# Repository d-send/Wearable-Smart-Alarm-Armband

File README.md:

# Wearable Smart Alarm Armband (Work in progress)

An Armband designed primaraly for force waking up in the morning using vibration and Electrical stimulation.Uses an android app to communicate via BLE for scheuling and monitering status such as battery capacity.Integrated IMU is used to detect weather the user is awake or sleeping.

## Features
* Wakeup sheduling capability through an android app via BLE
* reminders through vibrations
* two hardware buttons for additional functionalities
* extremely low power consumption
* detachable battery
* tightness adjestable strip (around arm)  

## PCB

## Finished Armband

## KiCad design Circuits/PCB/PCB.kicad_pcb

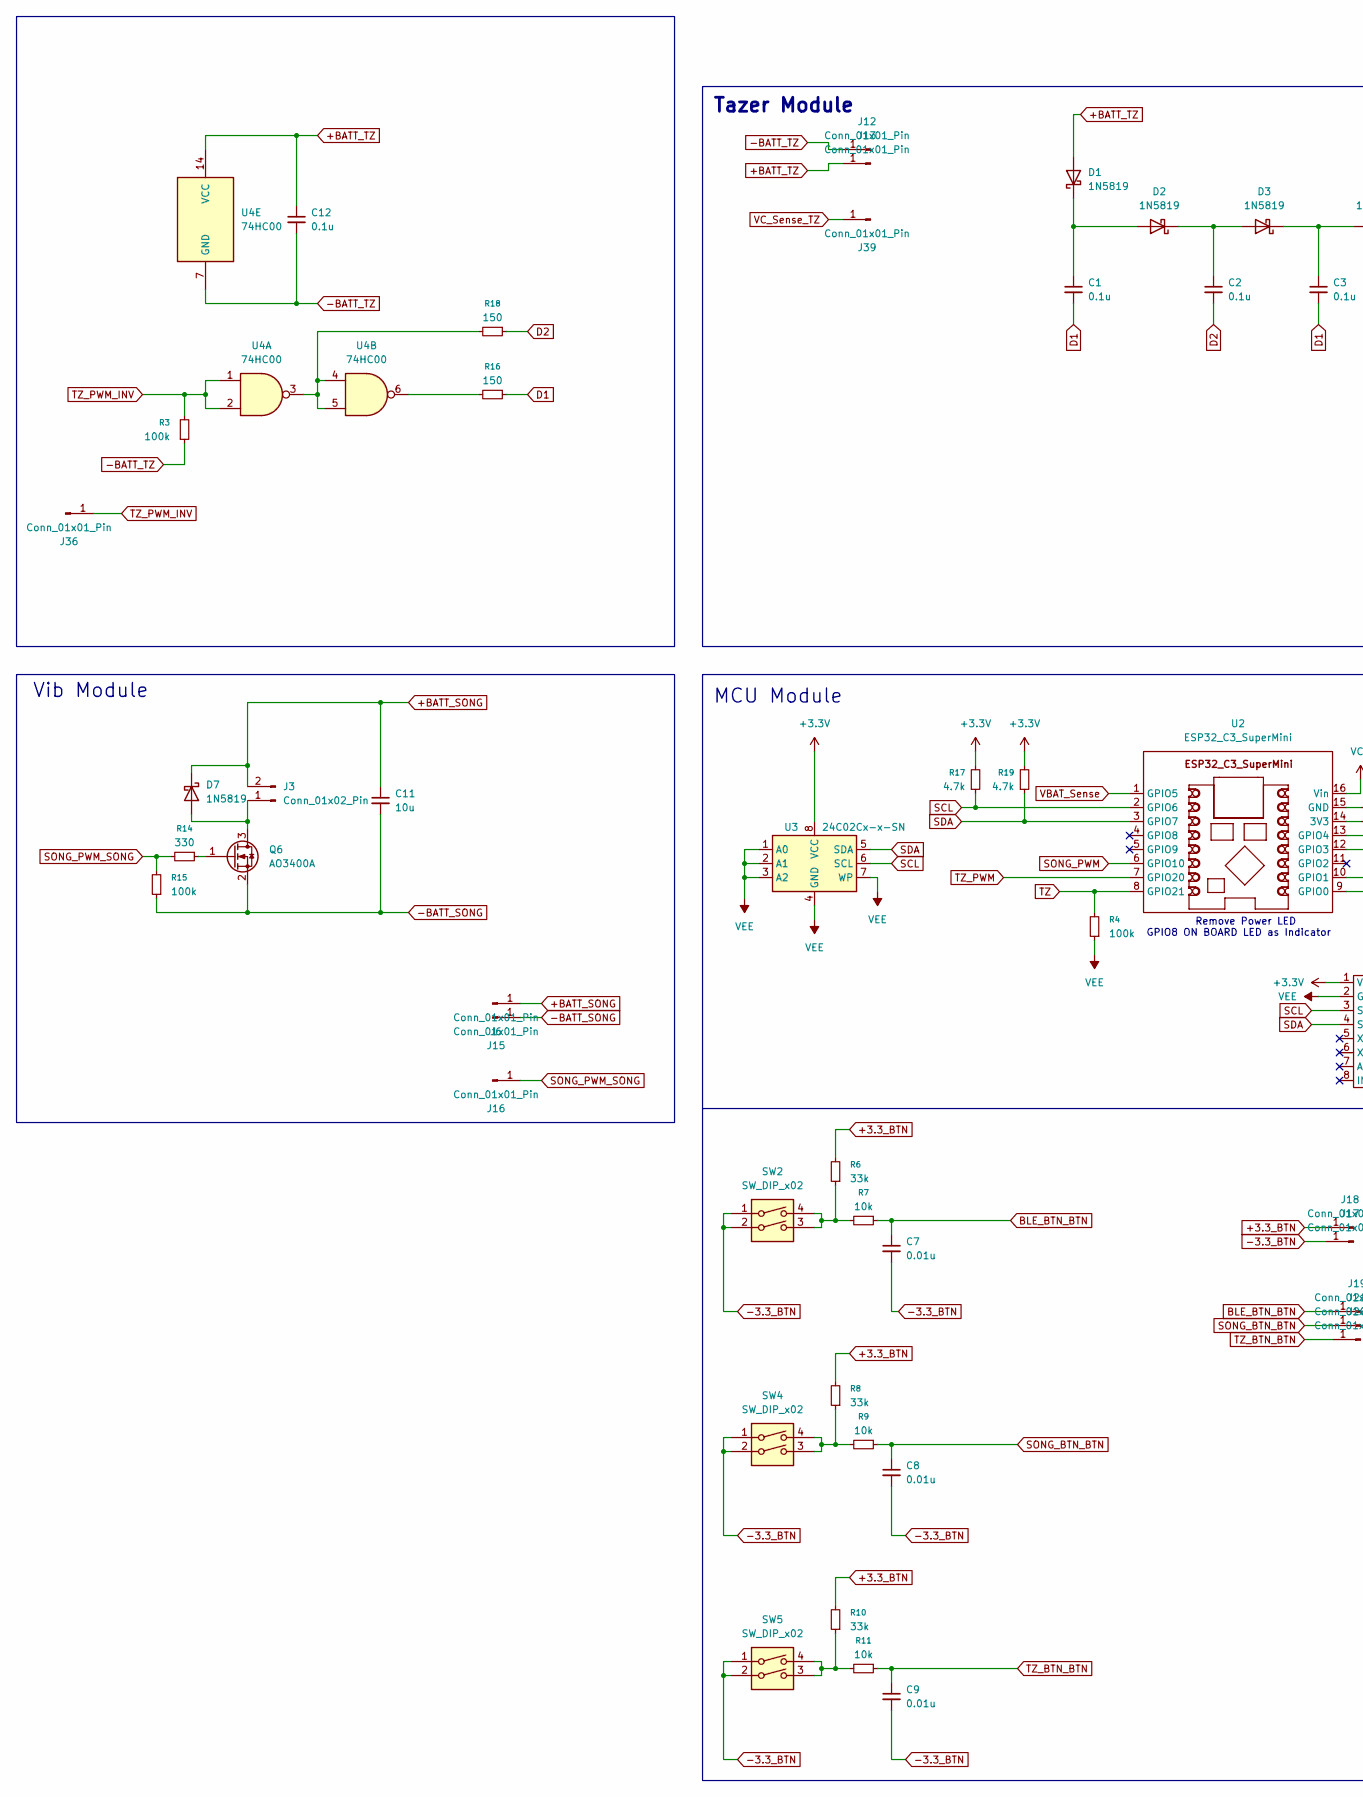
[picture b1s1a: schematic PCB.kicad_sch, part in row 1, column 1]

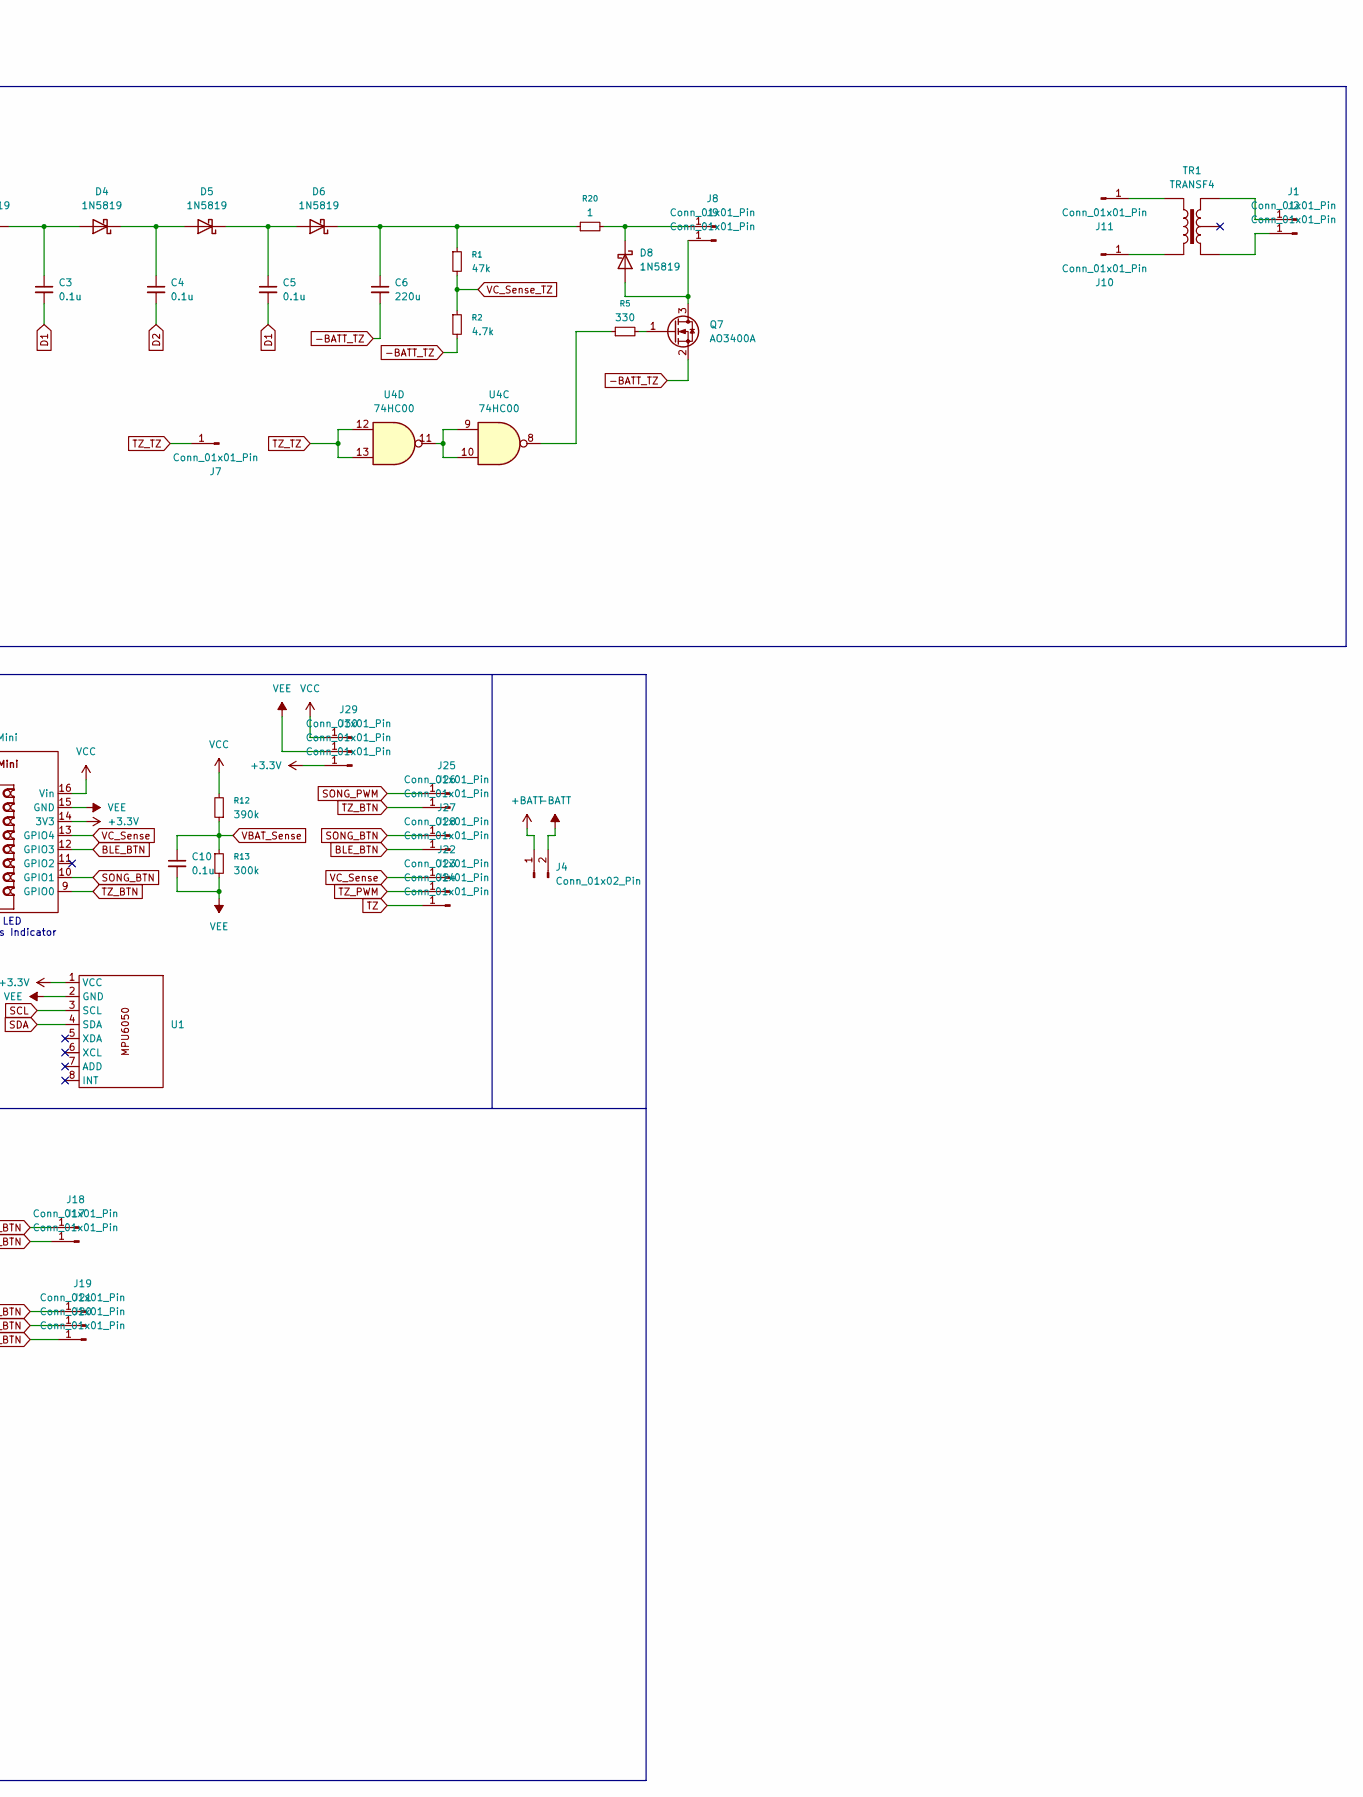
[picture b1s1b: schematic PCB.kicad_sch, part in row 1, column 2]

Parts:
C1, C2, C3, C4, C5, C10, C12: 0.1u; C_Disc_D5.0mm_W2.5mm_P2.50mm
C6: 220u; CP_Radial_D8.0mm_P3.80mm
C7, C8, C9: 0.01u; C_Disc_D5.0mm_W2.5mm_P2.50mm
C11: 10u; CP_Radial_D5.0mm_P2.50mm
D1, D2, D3, D4, D5, D6, D7, D8: 1N5819; D_DO-41_SOD81_P7.62mm_Horizontal
J1, J2: Conn_01x01_Pin; TestPoint_THTPad_2.0x2.0mm_Drill1.0mm
J3: Conn_01x02_Pin; TestPoint_2Pads_Pitch2.54mm_Drill0.8mm
J4: Conn_01x02_Pin; JST_XH_B2B-XH-A_1x02_P2.50mm_Vertical
J6, J7, J8, J9, J10, J11, J12, J13, J15, J16, J17, J18, J19, J20, J21, J22, J23, J24, J25, J26, J27, J28, J29, J30, J33, J36, J39: Conn_01x01_Pin; TestPoint_THTPad_D1.5mm_Drill0.7mm
Q6, Q7: AO3400A; SOT-23
R1: 47k; R_0603_1608Metric
R2, R17, R19: 4.7k; R_0603_1608Metric
R3, R15: 100k; R_Axial_DIN0207_L6.3mm_D2.5mm_P7.62mm_Horizontal
R4: 100k; R_Axial_DIN0207_L6.3mm_D2.5mm_P10.16mm_Horizontal
R5, R14: 330; R_Axial_DIN0207_L6.3mm_D2.5mm_P7.62mm_Horizontal
R6, R8, R10: 33k; R_0603_1608Metric
R7, R9, R11: 10k; R_0603_1608Metric
R12: 390k; R_1206_3216Metric
R13: 300k; R_1206_3216Metric
R16, R18: 150; R_1206_3216Metric
R20: 1; R_1206_3216Metric
SW2, SW4, SW5: SW_DIP_x02; DPDT_Switch
TR1: TRANSF4; 5pin Flyback Transformer
U1: MPU6050_Module
U2: ESP32_C3_SuperMini
U3: 24C02Cx-x-SN; DIP-8_W7.62mm
U4: 74HC00; DIP-14_W7.62mm

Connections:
+3.3V: J33.1, R17.2, R19.2, U1.1 (VCC), U2.14 (3V3), U3.8 (VCC)
+3.3_BTN: J18.1, R6.2, R8.2, R10.2
+BATT: J4.1
+BATT_SONG: C11.1, D7.1 (K), J3.2, J6.1
+BATT_TZ: C12.1, D1.2 (A), J13.1, U4.14 (VCC)
-3.3_BTN: C7.2, C8.2, C9.2, J17.1, SW2.1, SW2.2, SW4.1, SW4.2, SW5.1, SW5.2
-BATT: J4.2
-BATT_SONG: C11.2, J15.1, Q6.2 (S), R15.1
-BATT_TZ: C6.2, C12.2, J12.1, Q7.2 (S), R2.2, R3.1, U4.7 (GND)
BLE_BTN: J28.1, U2.12 (GPIO3)
BLE_BTN_BTN: C7.1, J19.1, R7.1
D1: C1.2, C3.2, C5.2, R16.1; also elsewhere on the board
D2: C2.2, C4.2, R18.1; also elsewhere on the board
unnamed: C1.1, D1.1 (K), D2.2 (A)
unnamed: C2.1, D2.1 (K), D3.2 (A)
unnamed: C3.1, D3.1 (K), D4.2 (A)
unnamed: C4.1, D4.1 (K), D5.2 (A)
unnamed: C5.1, D5.1 (K), D6.2 (A)
unnamed: C6.1, D6.1 (K), R1.1, R20.1
unnamed: D7.2 (A), J3.1, Q6.3 (D)
unnamed: D8.2 (A), J9.1, Q7.3 (D)
unnamed: D8.1 (K), J8.1, R20.2
unnamed: J1.1, TR1.3
unnamed: J2.1, TR1.1
unnamed: J10.1, TR1.5
unnamed: J11.1, TR1.4
unnamed: Q6.1 (G), R14.1
unnamed: Q7.1 (G), R5.2
unnamed: R5.1, U4.8
unnamed: R6.1, R7.2, SW2.3, SW2.4
unnamed: R8.1, R9.2, SW4.3, SW4.4
unnamed: R10.1, R11.2, SW5.3, SW5.4
unnamed: R16.2, U4.6
unnamed: R18.2, U4.3, U4.4, U4.5
unnamed: U4.9, U4.10, U4.11
SCL: R17.1, U1.3 (SCL), U2.2 (GPIO6), U3.6 (SCL)
SDA: R19.1, U1.4 (SDA), U2.3 (GPIO7), U3.5 (SDA)
SONG_BTN: J27.1, U2.10 (GPIO1)
SONG_BTN_BTN: C8.1, J21.1, R9.1
SONG_PWM: J25.1, U2.6 (GPIO10)
SONG_PWM_SONG: J16.1, R14.2, R15.2
TZ: J24.1, R4.2, U2.8 (GPIO21)
TZ_BTN: J26.1, U2.9 (GPIO0)
TZ_BTN_BTN: C9.1, J20.1, R11.1
TZ_PWM: J23.1, U2.7 (GPIO20)
TZ_PWM_INV: J36.1, R3.2, U4.1, U4.2
TZ_TZ: J7.1, U4.12, U4.13
VBAT_Sense: C10.1, R12.1, R13.1, U2.1 (GPIO5)
VCC: J29.1, R12.2, U2.16 (Vin)
VC_Sense: J22.1, U2.13 (GPIO4)
VC_Sense_TZ: J39.1, R1.2, R2.1
VEE: C10.2, J30.1, R4.1, R13.2, U1.2 (GND), U2.15 (GND), U3.1 (A0), U3.2 (A1), U3.3 (A2), U3.4 (GND), U3.7 (WP)

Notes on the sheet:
GPIO8 ON BOARD LED as Indicator
Remove Power LED
MCU Module
Vib Module
Tazer Module

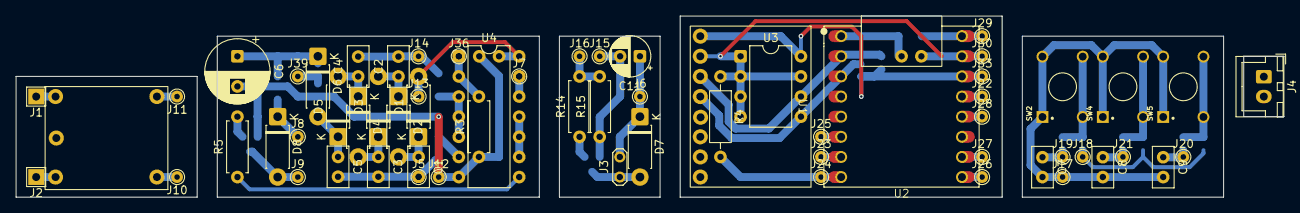
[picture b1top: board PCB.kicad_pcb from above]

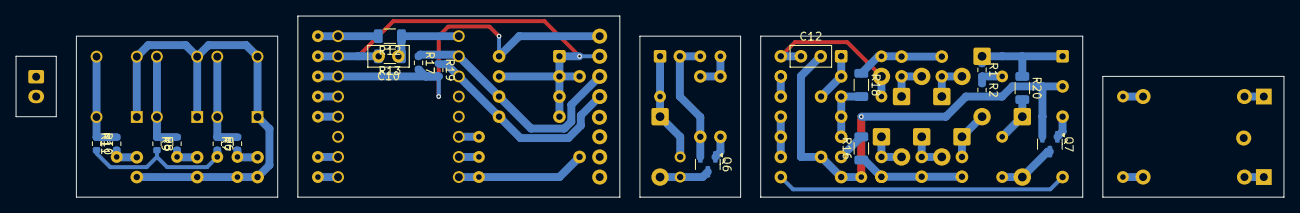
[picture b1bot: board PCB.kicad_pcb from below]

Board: 2 copper layers, 160.0 x 22.9 mm, 83 parts (19 on the bottom side), 50 nets.

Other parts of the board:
J5, J14: Conn_01x01_Pin; TestPoint_THTPad_D1.5mm_Drill0.7mm

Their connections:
D1: J5.1; also elsewhere on the board
D2: J14.1; also elsewhere on the board

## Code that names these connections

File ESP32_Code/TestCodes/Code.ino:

#include <Wire.h>


#define R_TOP 47000.0
#define R_BOTTOM 4700.0
#define ADC_REF 3.3
#define ADC_MAX 4095.0
#define VC_Sense 4
#define VBat_Sense 3
#define LED_Builtin 8

#define D_PWM 20
const int VC_Set = 15;
bool Dpwm_Enabled = true;

#define TZ_BTN 0
#define SONG_BTN 1

#define TZ 21

#define Song_PWM 10

#define SCL_PIN 6
#define SDA_PIN 7

#define EEPROM_ADDR 0x50   // 24C16 base address



void eepromWrite(uint16_t addr, uint8_t data)
{
  Wire.beginTransmission(EEPROM_ADDR | ((addr >> 8) & 0x07));
  Wire.write(addr & 0xFF);
  Wire.write(data);
  Wire.endTransmission();
  delay(5);
}

uint8_t eepromRead(uint16_t addr)
{
  Wire.beginTransmission(EEPROM_ADDR | ((addr >> 8) & 0x07));
  Wire.write(addr & 0xFF);
  Wire.endTransmission();

  Wire.requestFrom(EEPROM_ADDR | ((addr >> 8) & 0x07), 1);
  return Wire.read();
}

float readBatteryVoltage(uint8_t ADCpin,float R_top,float R_bottom)
{
  int adc = analogRead(ADCpin);
  float v = (adc / ADC_MAX) * ADC_REF;
  return v * ((R_top + R_bottom) / R_bottom);
}

volatile bool triggerPulse = false;
volatile uint32_t pulseWidth_us = 200;   // Change pulse width here

void IRAM_ATTR gpioInterrupt()
{
  // Interrupt fires on falling edge
  triggerPulse = true;
}

void setup() {
  // put your setup code here, to run once:
  Serial.begin(115200);
  
  pinMode(SONG_BTN,INPUT);
  pinMode(VC_Sense,INPUT);
  pinMode(TZ,OUTPUT);
  pinMode(LED_Builtin,OUTPUT);
  pinMode(Song_PWM,OUTPUT);
  pinMode(D_PWM,OUTPUT);
  ledcAttach(D_PWM,10000,8);
  pinMode(TZ_BTN,INPUT);
  attachInterrupt(digitalPinToInterrupt(TZ_BTN),
                  gpioInterrupt,
                  FALLING);

  digitalWrite(TZ,LOW);
  digitalWrite(LED_Builtin,HIGH);
  digitalWrite(Song_PWM,LOW);

  Wire.begin(SDA_PIN, SCL_PIN);

  ledcWrite(D_PWM, 128);
}

void loop() {
  // put your main code here, to run repeatedly:

  uint8_t v = eepromRead(0);
  uint8_t u = eepromRead(56);
  Serial.print(v);
  Serial.print("\t");
  Serial.print(u);
  Serial.print("\t");

  float vc = readBatteryVoltage(VC_Sense,47000.0,4700.0);

  if(vc > 18.0)
  {
    digitalWrite(LED_Builtin,LOW);
    ledcDetach(D_PWM);
    digitalWrite(D_PWM,LOW);
    Dpwm_Enabled = false;
  }
  else
  {
    if((vc < 8.0) && (Dpwm_Enabled == false))
    {
      Dpwm_Enabled = true;
      ledcAttach(D_PWM,10000,8);
      ledcWrite(D_PWM, 128);
      digitalWrite(LED_Builtin,HIGH);

    }
  }

  float vbat = readBatteryVoltage(VBat_Sense,390000.0,300000.0);
  vbat = (5*vbat/5.78);

  Serial.print(vc);
  Serial.print("\t");
  Serial.print(vbat);
  Serial.print("\t");

  if(digitalRead(SONG_BTN) == 0)
  { 
    digitalWrite(Song_PWM,HIGH);
  }
  else
  {
    digitalWrite(Song_PWM,LOW);
  }

  if (triggerPulse) 
  {
    triggerPulse = false;

    digitalWrite(TZ, HIGH);
    delayMicroseconds(pulseWidth_us);
    digitalWrite(TZ, LOW);
  }


  Serial.print(digitalRead(TZ_BTN));
  Serial.print("\t");

  
  Serial.print(digitalRead(SONG_BTN));
  Serial.println("\t");


}

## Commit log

2026-03-20 Initial Upload
